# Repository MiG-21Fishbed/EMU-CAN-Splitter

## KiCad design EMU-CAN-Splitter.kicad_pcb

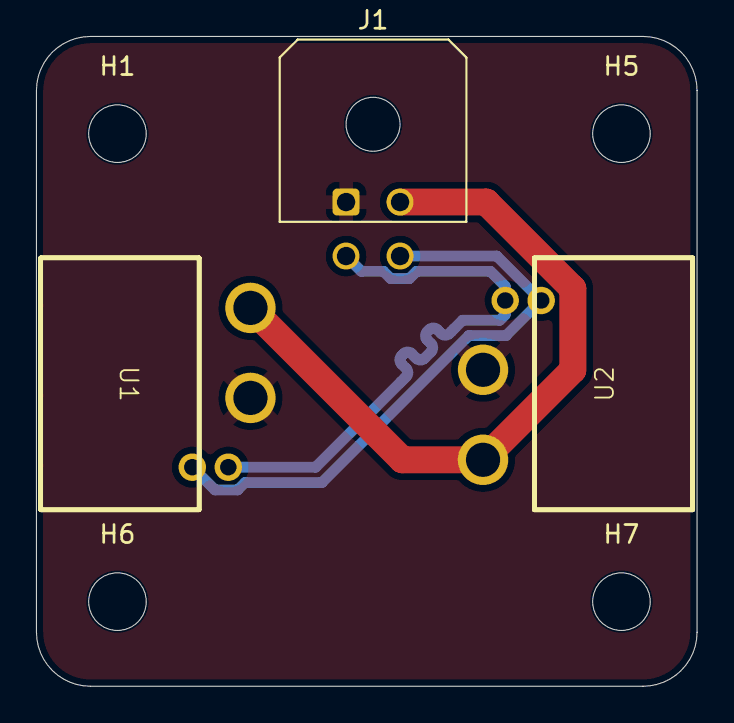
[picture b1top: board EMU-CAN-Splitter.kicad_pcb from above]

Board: 2 copper layers, 36.7 x 36.1 mm, 7 parts (0 on the bottom side), 4 nets.

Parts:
H1, H5, H6, H7: MountingHole; MountingHole_3.2mm_M3_DIN965
J1: Conn_02x02_Top_Bottom; Molex_Micro-Fit_3.0_43045-0400_2x02_P3.00mm_Horizontal
U1, U2: XT30PW (2+2); XT30PW_(2+2)

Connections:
/CAN+: J1.4, U1.4 (CANH), U2.4 (CANH)
/CAN-: J1.3, U1.3 (CANL), U2.3 (CANL)
unnamed: J1.1, U1.2 (GND), U2.2 (GND)
unnamed: J1.2, U1.1 (VIN), U2.1 (VIN)

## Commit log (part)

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2026-04-10 EMU CAN Splittet
